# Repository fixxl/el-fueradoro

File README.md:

# el-fueradoro

This project contains a remotely controlled ignition system for audio-fireworks based on ATmega328P and RFM69CW.
Further information (in German) is given in [the user manual](https://cdn.jsdelivr.net/gh/fixxl/el-fueradoro@master/Manual/fueradoro.pdf).

What the system is capable of doing can be seen in our [new year's fireworks 2015](https://vimeo.com/116115628), [new year's fireworks 2016](https://vimeo.com/150594996), [new year's fireworks 2017](https://www.youtube.com/watch?v=Rc5oZRx3s50), [new year's fireworks 2018](https://www.youtube.com/watch?v=unH9tJSg1mw), and [new year's fireworks 2019](https://www.youtube.com/watch?v=GiKSdqZKpVQ).

Copyright:

All parts of the project are licensed under: https://creativecommons.org/licenses/by-nc/3.0/de/

Usage to perform commercial firework shows is explicitly granted.
Selling hard- and software derived from this project and usage within commercial systems is prohibited.

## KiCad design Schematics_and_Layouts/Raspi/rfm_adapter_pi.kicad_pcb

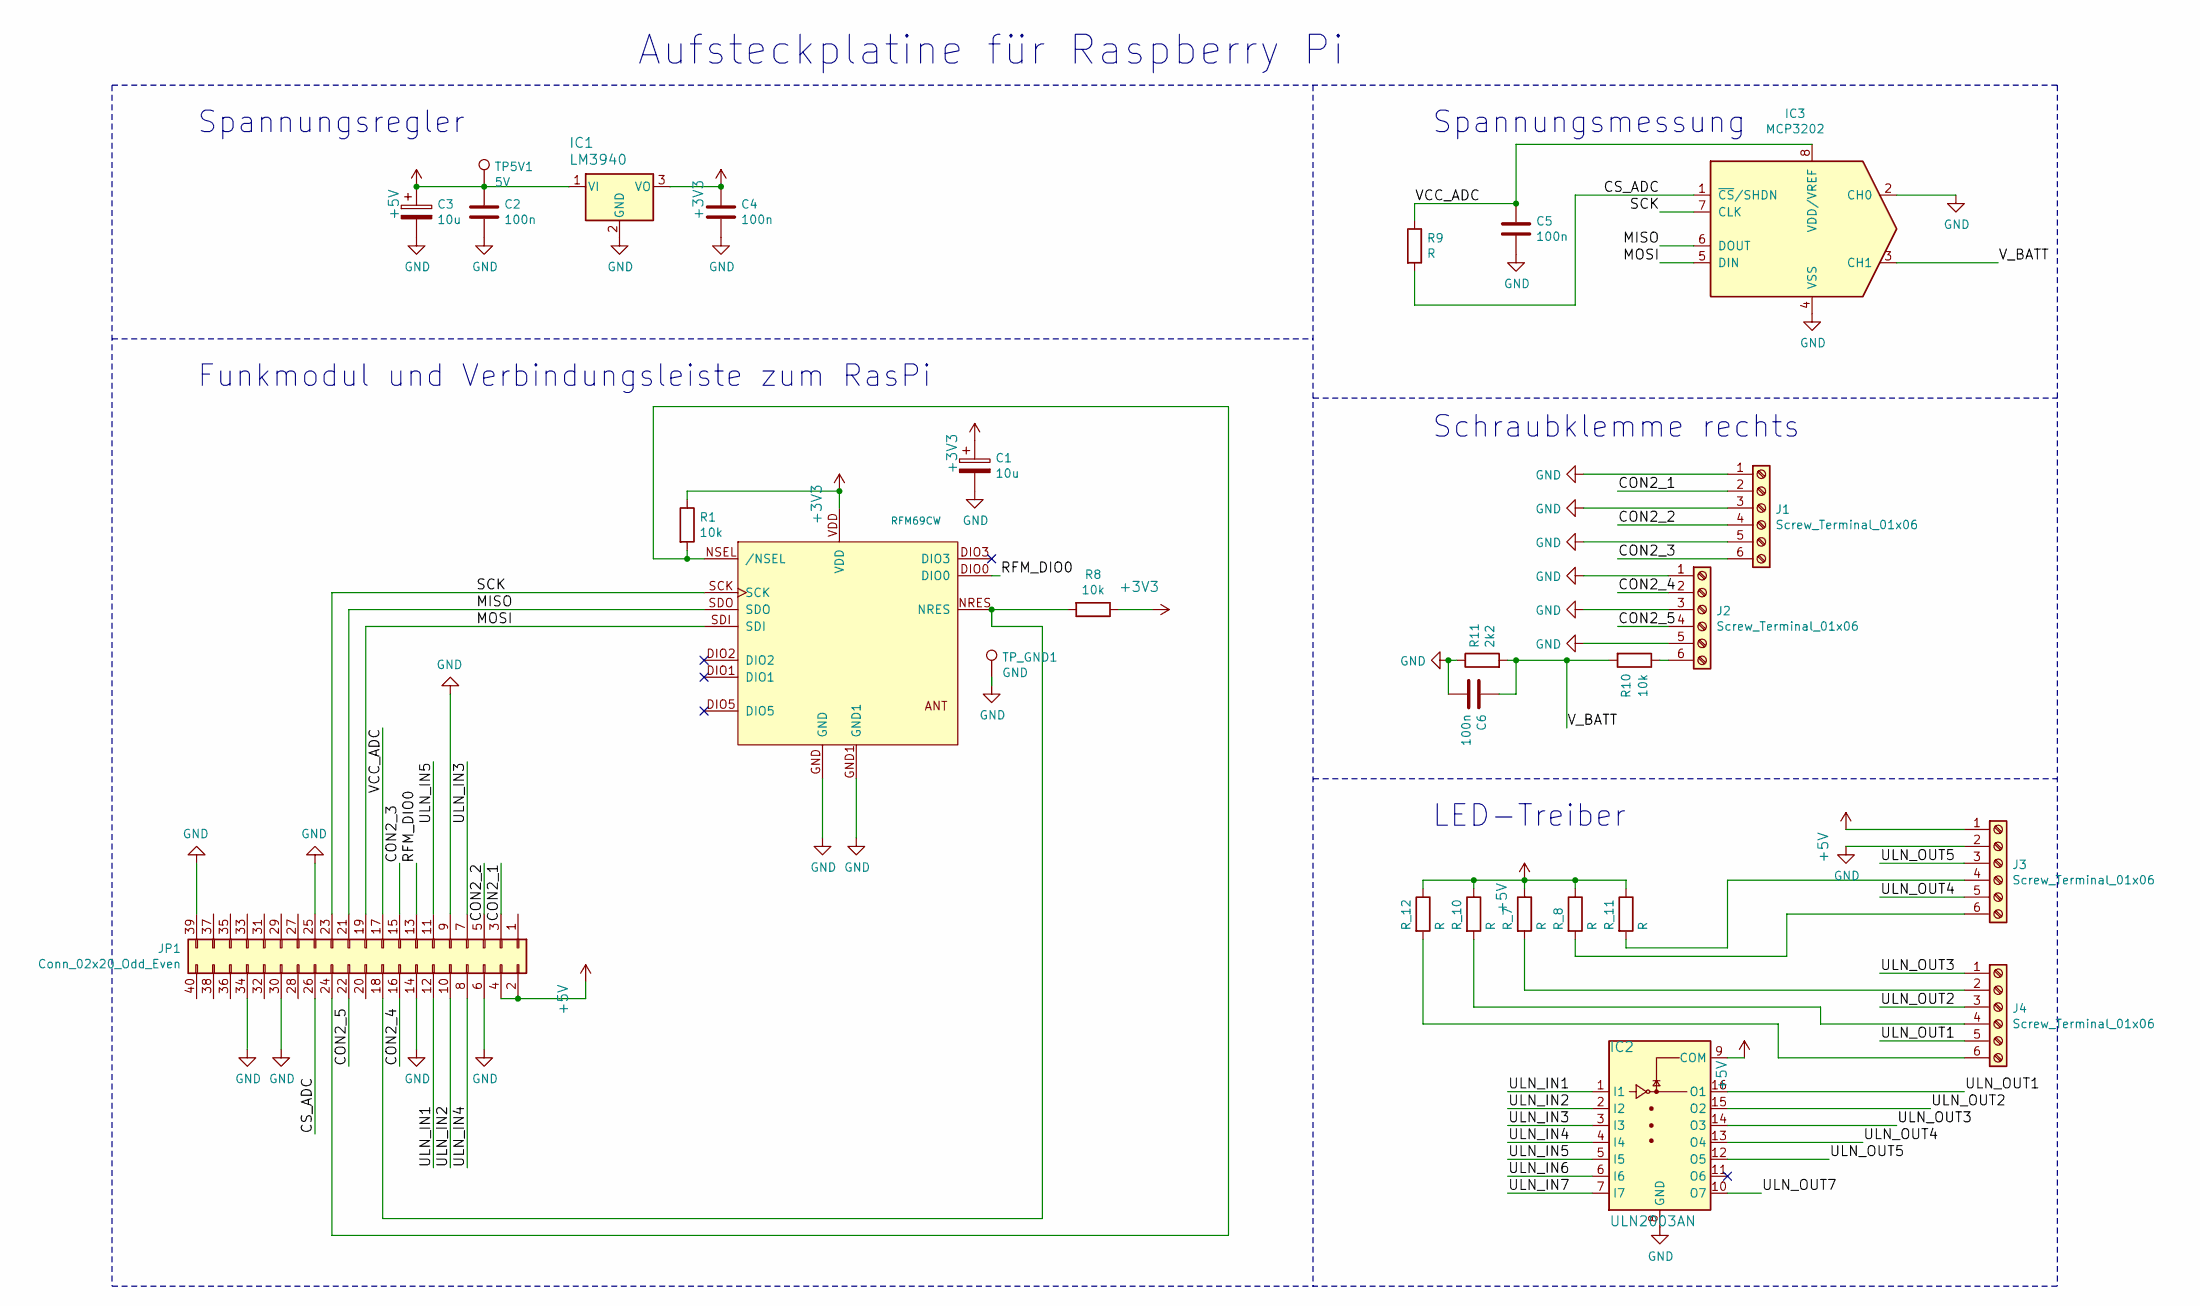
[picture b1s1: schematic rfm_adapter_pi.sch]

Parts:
C1, C3: 10u; CP_Radial_D5.0mm_P2.50mm
C2, C4, C5, C6: 100n; C_Disc_D5.0mm_W2.5mm_P2.50mm
IC1: LM3940; TO-220-3_Vertical
IC2: ULN2003AN; DIP-16_W7.62mm
IC3: MCP3202; DIP-8_W7.62mm
J1, J2, J3, J4: Screw_Terminal_01x06; TerminalBlock_MetzConnect_Type059_RT06306HBWC_1x06_P3.50mm
JP1: Conn_02x20_Odd_Even; PinSocket_2x20_P2.54mm_Vertical
R1, R8, R10: 10k; R_Axial_DIN0207_L6.3mm_D2.5mm_P10.16mm_Horizontal
R9: R; R_Axial_DIN0207_L6.3mm_D2.5mm_P10.16mm_Horizontal
R11: 2k2; R_Axial_DIN0207_L6.3mm_D2.5mm_P10.16mm_Horizontal
R_7, R_8, R_10, R_11, R_12: R; R_Axial_DIN0207_L6.3mm_D2.5mm_P10.16mm_Horizontal
TP5V1: 5V; TestPoint_THTPad_D1.5mm_Drill0.7mm
TP_GND1: GND; TestPoint_THTPad_D1.5mm_Drill0.7mm
U$1: RFM69CW

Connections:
+3V3: C1.1, C4.1, IC1.3 (VO), R1.1, R8.1, U$1.VDD
+5V: C2.1, C3.1, IC1.1 (VI), IC2.9 (COM), J3.1, JP1.2, JP1.4, R_7.1, R_8.1, R_10.1, R_11.1, R_12.1, TP5V1.1
/CON2_1: J1.2, JP1.3
/CON2_2: J1.4, JP1.5
/CON2_3: J1.6, JP1.15
/CON2_4: J2.2, JP1.16
/CON2_5: J2.4, JP1.22
/CS_ADC: IC3.1 (~CS~/SHDN), JP1.26, R9.2
/MISO: IC3.6 (DOUT), JP1.21, U$1.SDO
/MOSI: IC3.5 (DIN), JP1.19, U$1.SDI
/RFM_DIO0: JP1.13, U$1.DIO0
/SCK: IC3.7 (CLK), JP1.23, U$1.SCK
/ULN_IN1: IC2.1 (I1), JP1.12
/ULN_IN2: IC2.2 (I2), JP1.10
/ULN_IN3: IC2.3 (I3), JP1.7
/ULN_IN4: IC2.4 (I4), JP1.8
/ULN_IN5: IC2.5 (I5), JP1.11
/ULN_IN6: IC2.6 (I6)
/ULN_IN7: IC2.7 (I7)
/ULN_OUT1: IC2.16 (O1), J4.5
/ULN_OUT2: IC2.15 (O2), J4.3
/ULN_OUT3: IC2.14 (O3), J4.1
/ULN_OUT4: IC2.13 (O4), J3.5
/ULN_OUT5: IC2.12 (O5), J3.3
/ULN_OUT7: IC2.10 (O7)
/VCC_ADC: C5.1, IC3.8 (VDD/VREF), JP1.17, R9.1
/V_BATT: C6.1, IC3.3 (CH1), R10.2, R11.2
GND: C1.2, C2.2, C3.2, C4.2, C5.2, C6.2, IC1.2 (GND), IC2.8 (GND), IC3.2 (CH0), IC3.4 (VSS), J1.1, J1.3, J1.5, J2.1, J2.3, J2.5, J3.2, JP1.6, JP1.9, JP1.14, JP1.25, JP1.30, JP1.34, JP1.39, R11.1, TP_GND1.1, U$1.GND, U$1.GND1
unnamed: J2.6, R10.1
unnamed: J3.4, R_11.2
unnamed: J3.6, R_8.2
unnamed: J4.2, R_7.2
unnamed: J4.4, R_10.2
unnamed: J4.6, R_12.2
unnamed: JP1.18, R8.2, U$1.NRES
unnamed: JP1.24, R1.2, U$1.NSEL (/NSEL)

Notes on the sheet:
Aufsteckplatine für Raspberry Pi
LED-Treiber
Schraubklemme rechts
Spannungsmessung
Spannungsregler
Funkmodul und Verbindungsleiste zum RasPi

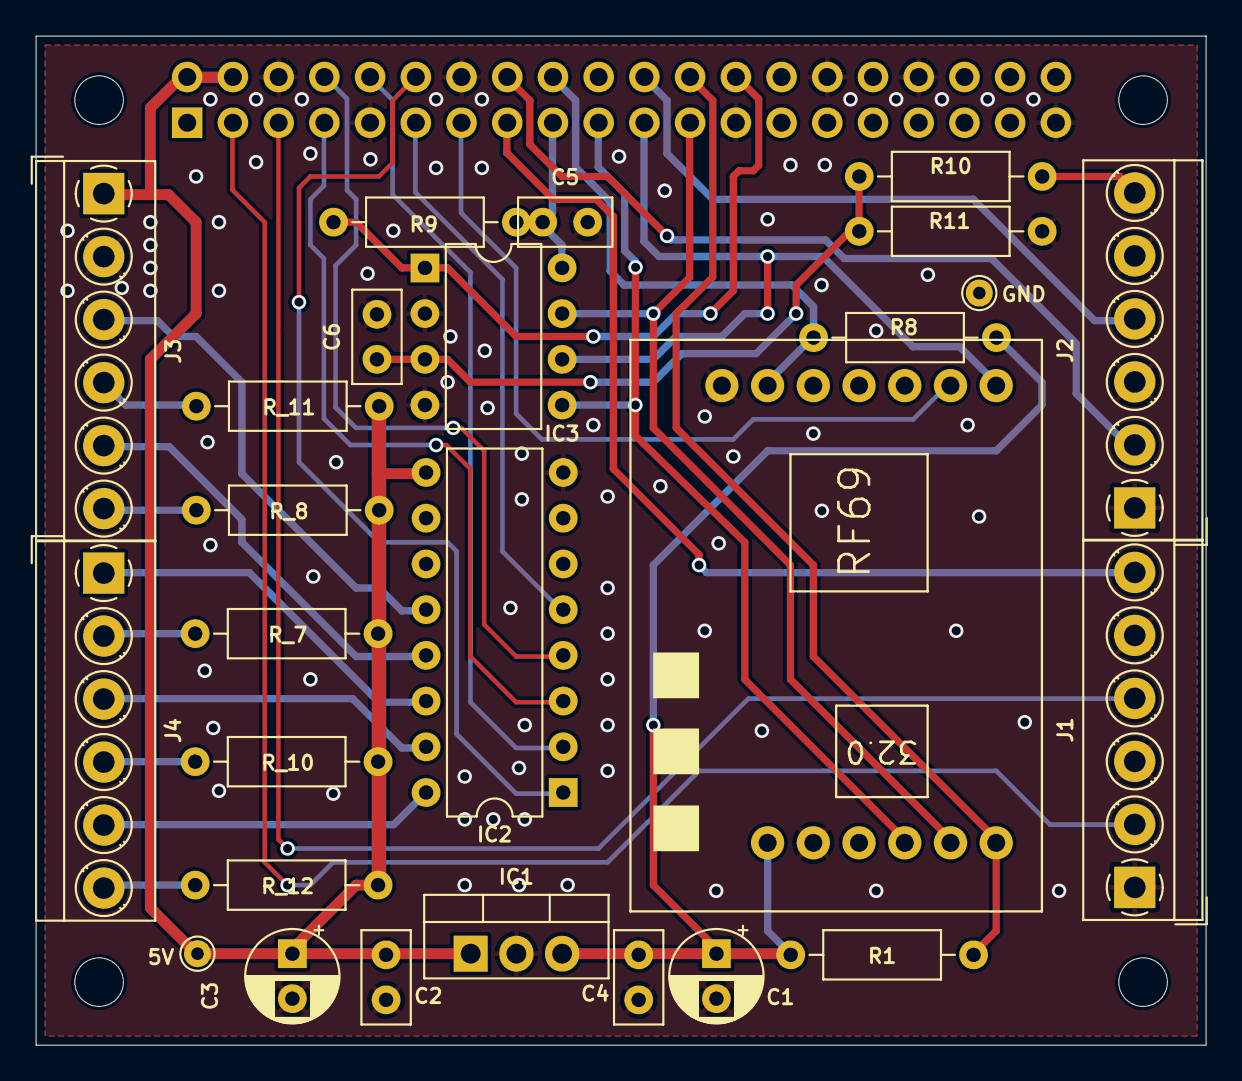
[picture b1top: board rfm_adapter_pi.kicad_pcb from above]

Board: 2 copper layers, 65.0 x 56.1 mm, 27 parts (0 on the bottom side), 33 nets.

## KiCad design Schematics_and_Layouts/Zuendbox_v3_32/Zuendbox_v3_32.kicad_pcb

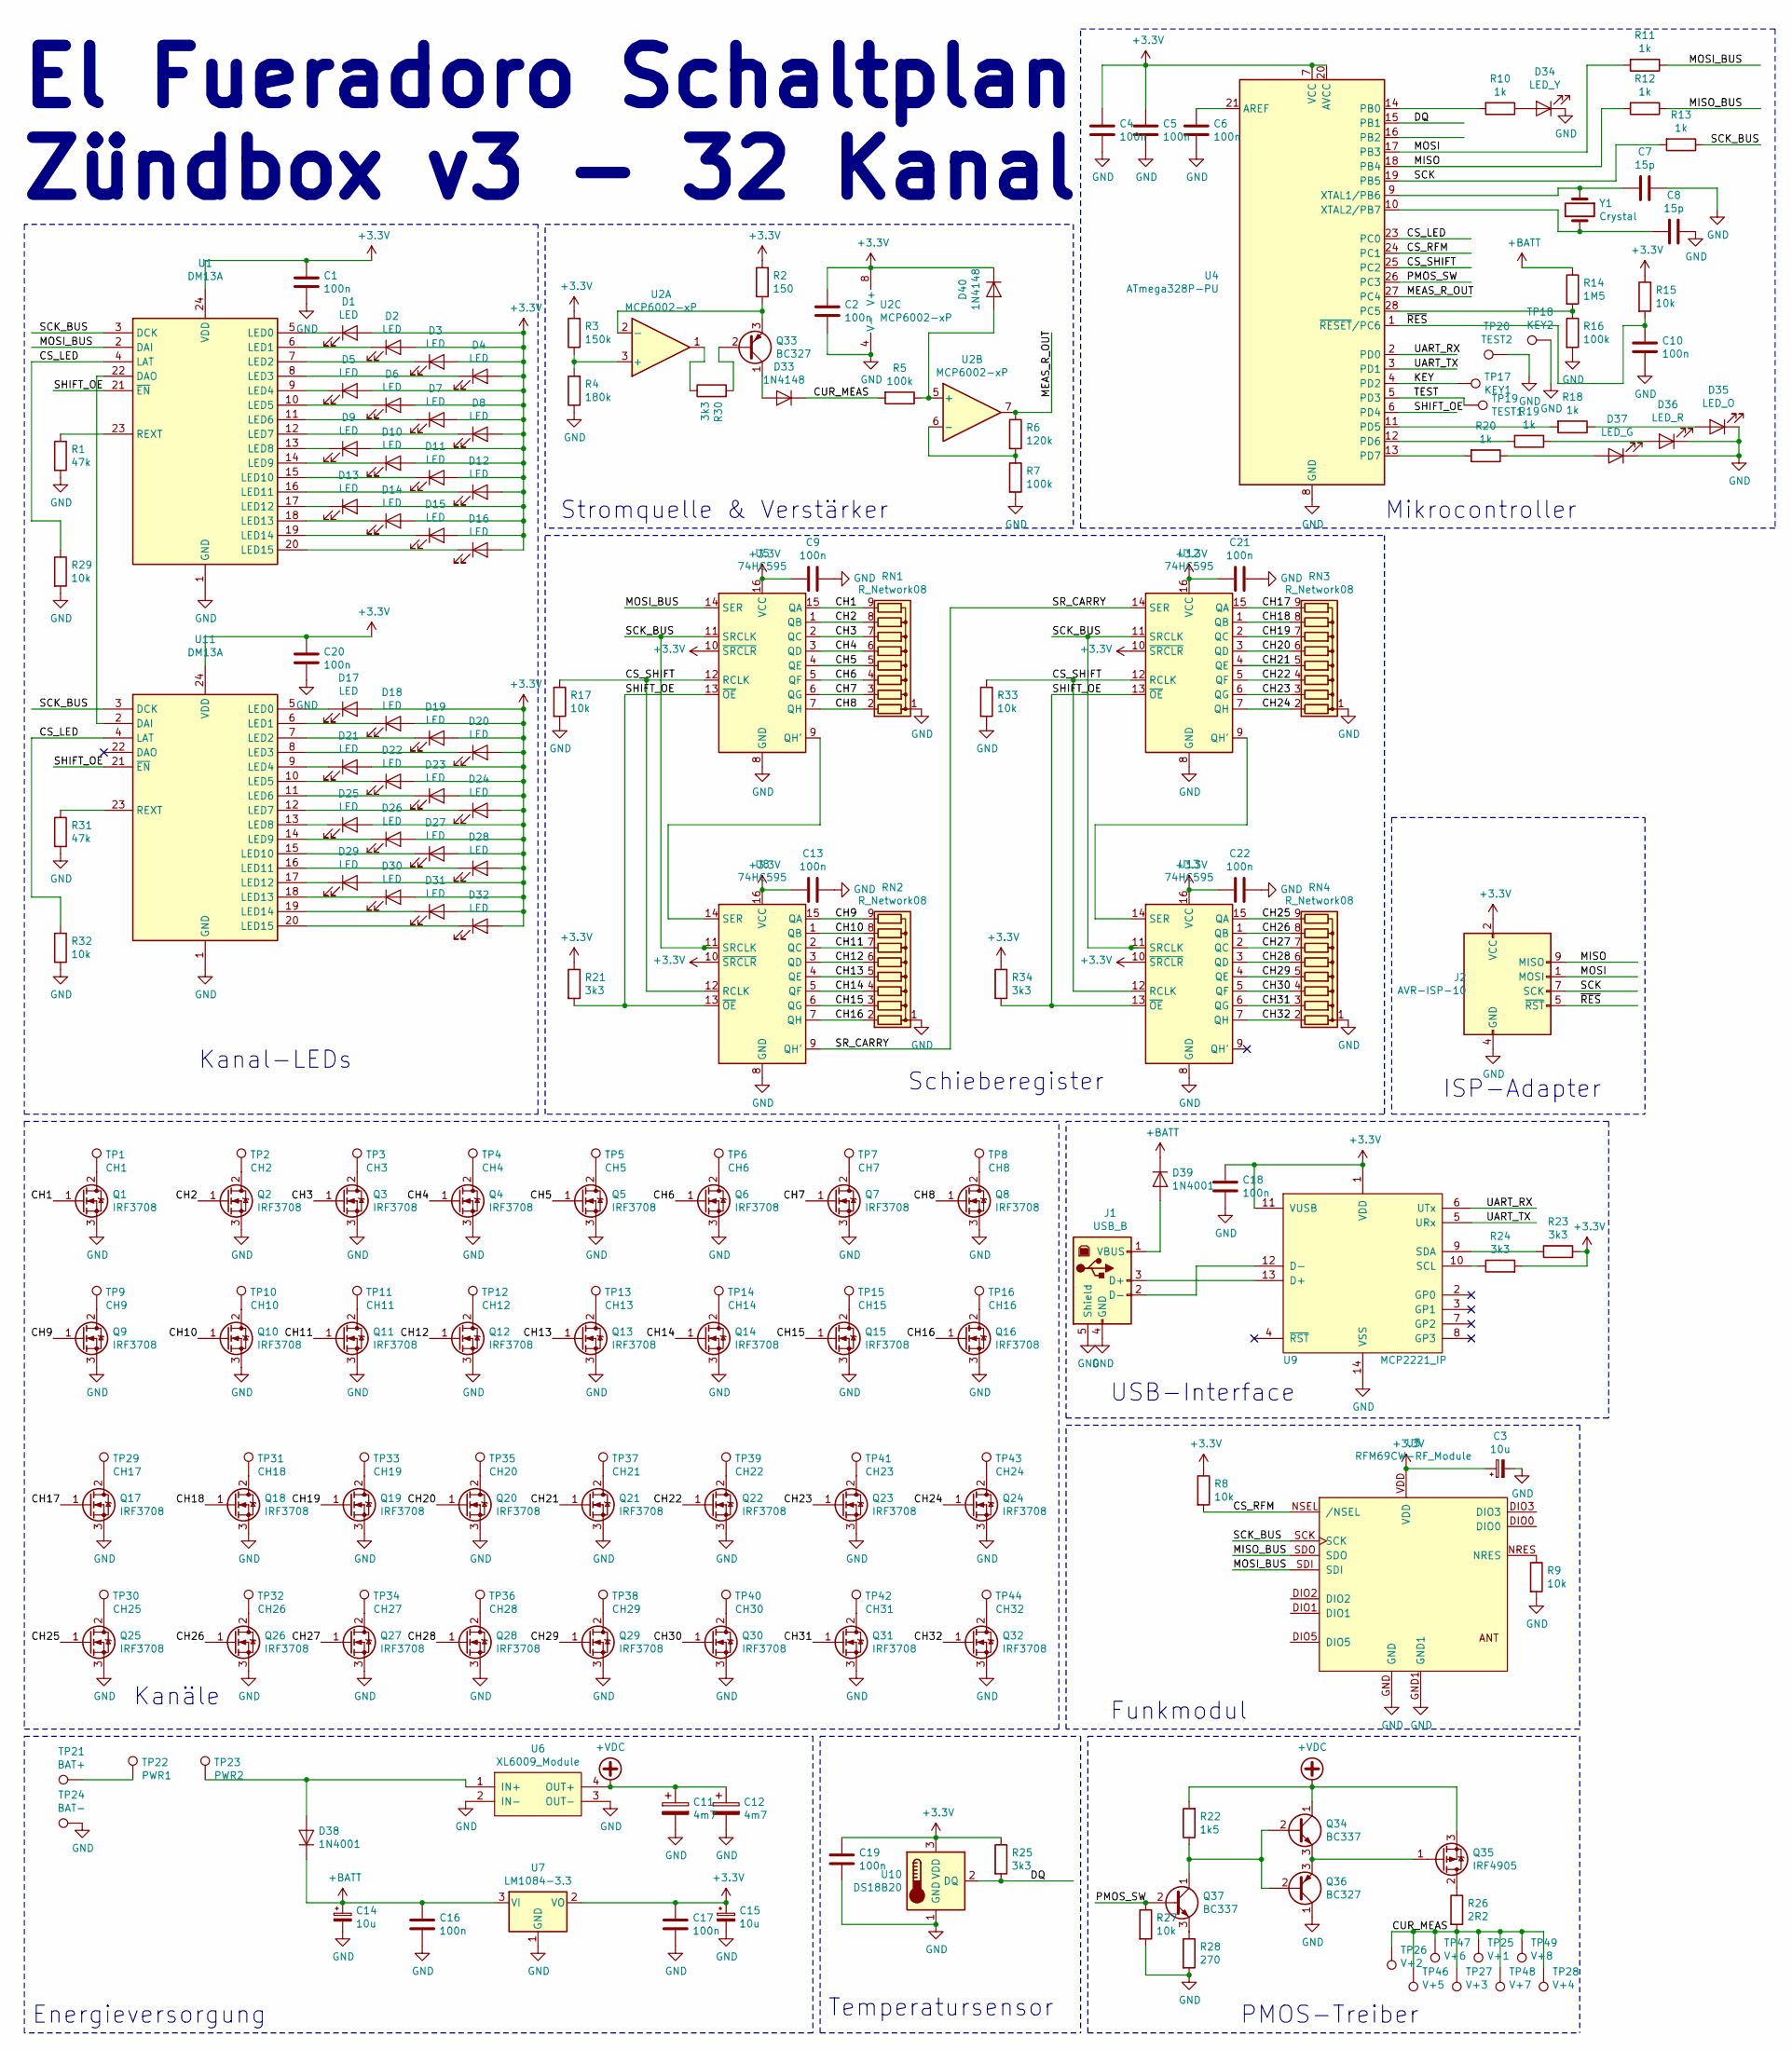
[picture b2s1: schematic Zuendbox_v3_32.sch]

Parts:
C1, C2, C4, C5, C6, C9, C10, C13, C16, C17, C18, C19, C20, C21, C22: 100n; C_Disc_D3.8mm_W2.6mm_P2.50mm
C3, C14, C15: 10u; CP_Radial_D6.3mm_P2.50mm
C7, C8: 15p; C_Disc_D3.8mm_W2.6mm_P2.50mm
C11, C12: 4m7; CP_Radial_D18.0mm_P7.50mm
D1, D2, D3, D4, D5, D6, D7, D8, D9, D10, D11, D12, D13, D14, D15, D16, D17, D18, D19, D20, D21, D22, D23, D24, D25, D26, D27, D28, D29, D30, D31, D32: LED; PinSocket_1x02_P2.54mm_Vertical
D33, D40: 1N4148; D_DO-35_SOD27_P7.62mm_Horizontal
D34: LED_Y; LED_D5.0mm
D35: LED_O; LED_D5.0mm
D36: LED_R; LED_D5.0mm
D37: LED_G; LED_D5.0mm
D38, D39: 1N4001; D_DO-41_SOD81_P10.16mm_Horizontal
J1: USB_B; USB_B_THT_Horizontal
J2: AVR-ISP-10; IDC-Header_2x05_P2.54mm_Vertical
Q1, Q2, Q3, Q4, Q5, Q6, Q7, Q8, Q9, Q10, Q11, Q12, Q13, Q14, Q15, Q16, Q17, Q18, Q19, Q20, Q21, Q22, Q23, Q24, Q25, Q26, Q27, Q28, Q29, Q30, Q31, Q32: IRF3708; TO-220-3_Vertical
Q33, Q36: BC327; TO-92_Inline_Wide
Q34, Q37: BC337; TO-92_Inline_Wide
Q35: IRF4905; TO-220-3_Vertical
R1, R31: 47k; R_Axial_DIN0207_L6.3mm_D2.5mm_P10.16mm_Horizontal
R2: 150; R_Axial_DIN0207_L6.3mm_D2.5mm_P10.16mm_Horizontal
R3: 150k; R_Axial_DIN0207_L6.3mm_D2.5mm_P10.16mm_Horizontal
R4: 180k; R_Axial_DIN0207_L6.3mm_D2.5mm_P10.16mm_Horizontal
R5, R7, R16: 100k; R_Axial_DIN0207_L6.3mm_D2.5mm_P10.16mm_Horizontal
R6: 120k; R_Axial_DIN0207_L6.3mm_D2.5mm_P10.16mm_Horizontal
R8, R9, R15, R17, R27, R29, R32, R33: 10k; R_Axial_DIN0207_L6.3mm_D2.5mm_P10.16mm_Horizontal
R10, R11, R12, R13, R18, R19, R20: 1k; R_Axial_DIN0207_L6.3mm_D2.5mm_P10.16mm_Horizontal
R14: 1M5; R_Axial_DIN0207_L6.3mm_D2.5mm_P10.16mm_Horizontal
R21, R23, R24, R25, R30, R34: 3k3; R_Axial_DIN0207_L6.3mm_D2.5mm_P10.16mm_Horizontal
R22: 1k5; R_Axial_DIN0207_L6.3mm_D2.5mm_P10.16mm_Horizontal
R26: 2R2; R_Radial_Power_L9.0mm_W10.0mm_Px2.90mm_Py2.40mm
R28: 270; R_Axial_DIN0207_L6.3mm_D2.5mm_P10.16mm_Horizontal
RN1, RN2, RN3, RN4: R_Network08; R_Array_SIP9
TP1: CH1; TestPoint_THTPad_D2.5mm_Drill1.2mm
TP2: CH2; TestPoint_THTPad_D2.5mm_Drill1.2mm
TP3: CH3; TestPoint_THTPad_D2.5mm_Drill1.2mm
TP4: CH4; TestPoint_THTPad_D2.5mm_Drill1.2mm
TP5: CH5; TestPoint_THTPad_D2.5mm_Drill1.2mm
TP6: CH6; TestPoint_THTPad_D2.5mm_Drill1.2mm
TP7: CH7; TestPoint_THTPad_D2.5mm_Drill1.2mm
TP8: CH8; TestPoint_THTPad_D2.5mm_Drill1.2mm
TP9: CH9; TestPoint_THTPad_D2.5mm_Drill1.2mm
TP10: CH10; TestPoint_THTPad_D2.5mm_Drill1.2mm
TP11: CH11; TestPoint_THTPad_D2.5mm_Drill1.2mm
TP12: CH12; TestPoint_THTPad_D2.5mm_Drill1.2mm
TP13: CH13; TestPoint_THTPad_D2.5mm_Drill1.2mm
TP14: CH14; TestPoint_THTPad_D2.5mm_Drill1.2mm
TP15: CH15; TestPoint_THTPad_D2.5mm_Drill1.2mm
TP16: CH16; TestPoint_THTPad_D2.5mm_Drill1.2mm
TP17: KEY1; TestPoint_THTPad_D2.5mm_Drill1.2mm
TP18: KEY2; TestPoint_THTPad_D2.5mm_Drill1.2mm
TP19: TEST1; TestPoint_THTPad_D2.5mm_Drill1.2mm
TP20: TEST2; TestPoint_THTPad_D2.5mm_Drill1.2mm
TP21: BAT+; TestPoint_THTPad_D2.5mm_Drill1.2mm
TP22: PWR1; TestPoint_THTPad_D2.5mm_Drill1.2mm
TP23: PWR2; TestPoint_THTPad_D2.5mm_Drill1.2mm
TP24: BAT-; TestPoint_THTPad_D2.5mm_Drill1.2mm
TP25: V+1; TestPoint_THTPad_D2.5mm_Drill1.2mm
TP26: V+2; TestPoint_THTPad_D2.5mm_Drill1.2mm
TP27: V+3; TestPoint_THTPad_D2.5mm_Drill1.2mm
TP28: V+4; TestPoint_THTPad_D2.5mm_Drill1.2mm
TP29: CH17; TestPoint_THTPad_D2.5mm_Drill1.2mm
TP30: CH25; TestPoint_THTPad_D2.5mm_Drill1.2mm
TP31: CH18; TestPoint_THTPad_D2.5mm_Drill1.2mm
TP32: CH26; TestPoint_THTPad_D2.5mm_Drill1.2mm
TP33: CH19; TestPoint_THTPad_D2.5mm_Drill1.2mm
TP34: CH27; TestPoint_THTPad_D2.5mm_Drill1.2mm
TP35: CH20; TestPoint_THTPad_D2.5mm_Drill1.2mm
TP36: CH28; TestPoint_THTPad_D2.5mm_Drill1.2mm
TP37: CH21; TestPoint_THTPad_D2.5mm_Drill1.2mm
TP38: CH29; TestPoint_THTPad_D2.5mm_Drill1.2mm
TP39: CH22; TestPoint_THTPad_D2.5mm_Drill1.2mm
TP40: CH30; TestPoint_THTPad_D2.5mm_Drill1.2mm
TP41: CH23; TestPoint_THTPad_D2.5mm_Drill1.2mm
TP42: CH31; TestPoint_THTPad_D2.5mm_Drill1.2mm
TP43: CH24; TestPoint_THTPad_D2.5mm_Drill1.2mm
TP44: CH32; TestPoint_THTPad_D2.5mm_Drill1.2mm
TP46: V+5; TestPoint_THTPad_D2.5mm_Drill1.2mm
TP47: V+6; TestPoint_THTPad_D2.5mm_Drill1.2mm
TP48: V+7; TestPoint_THTPad_D2.5mm_Drill1.2mm
TP49: V+8; TestPoint_THTPad_D2.5mm_Drill1.2mm
U1, U11: DM13A; DIP-24_W7.62mm
U2: MCP6002-xP; DIP-8_W7.62mm
U3: RFM69CW-RF_Module; RFM69CW
U4: ATmega328P-PU; DIP-28_W7.62mm
U5, U8, U12, U13: 74HC595; DIP-16_W7.62mm
U6: XL6009_Module; XL6009_STEP-UP-MODULE
U7: LM1084-3.3; TO-220-3_Horizontal_TabDown
U9: MCP2221_IP; DIP-14_W7.62mm
U10: DS18B20; TO-92_Inline_Wide
Y1: Crystal; Crystal_HC49-U_Vertical

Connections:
+3V3: C1.1, C2.1, C3.1, C4.2, C5.2, C9.2, C13.2, C15.1, C17.2, C18.2, C19.2, C20.1, C21.2, C22.2, D1.2 (A), D2.2 (A), D3.2 (A), D4.2 (A), D5.2 (A), D6.2 (A), D7.2 (A), D8.2 (A), D9.2 (A), D10.2 (A), D11.2 (A), D12.2 (A), D13.2 (A), D14.2 (A), D15.2 (A), D16.2 (A), D17.2 (A), D18.2 (A), D19.2 (A), D20.2 (A), D21.2 (A), D22.2 (A), D23.2 (A), D24.2 (A), D25.2 (A), D26.2 (A), D27.2 (A), D28.2 (A), D29.2 (A), D30.2 (A), D31.2 (A), D32.2 (A), D40.1 (K), J2.2 (VCC), R2.2, R3.2, R8.1, R15.1, R21.1, R23.2, R24.2, R25.1, R34.1, U1.24 (VDD), U2.8 (V+), U3.VDD, U4.7 (VCC), U4.20 (AVCC), U5.10 (~SRCLR), U5.16 (VCC), U7.2 (VO), U8.10 (~SRCLR), U8.16 (VCC), U9.1 (VDD), U9.11 (VUSB), U10.3 (VDD), U11.24 (VDD), U12.10 (~SRCLR), U12.16 (VCC), U13.10 (~SRCLR), U13.16 (VCC)
+BATT: C14.1, C16.2, D38.1 (K), D39.1 (K), R14.1, U7.3 (VI)
+VDC: C11.1, C12.1, Q34.1 (C), Q35.3 (S), R22.2, U6.4 (OUT+)
/CH1: Q1.1 (G), RN1.9 (R8), U5.15 (QA)
/CH2: Q2.1 (G), RN1.8 (R7), U5.1 (QB)
/CH3: Q3.1 (G), RN1.7 (R6), U5.2 (QC)
/CH4: Q4.1 (G), RN1.6 (R5), U5.3 (QD)
/CH5: Q5.1 (G), RN1.5 (R4), U5.4 (QE)
/CH6: Q6.1 (G), RN1.4 (R3), U5.5 (QF)
/CH7: Q7.1 (G), RN1.3 (R2), U5.6 (QG)
/CH8: Q8.1 (G), RN1.2 (R1), U5.7 (QH)
/CH9: Q9.1 (G), RN2.9 (R8), U8.15 (QA)
/CH10: Q10.1 (G), RN2.8 (R7), U8.1 (QB)
/CH11: Q11.1 (G), RN2.7 (R6), U8.2 (QC)
/CH12: Q12.1 (G), RN2.6 (R5), U8.3 (QD)
/CH13: Q13.1 (G), RN2.5 (R4), U8.4 (QE)
/CH14: Q14.1 (G), RN2.4 (R3), U8.5 (QF)
/CH15: Q15.1 (G), RN2.3 (R2), U8.6 (QG)
/CH16: Q16.1 (G), RN2.2 (R1), U8.7 (QH)
/CH17: Q17.1 (G), RN3.9 (R8), U12.15 (QA)
/CH18: Q18.1 (G), RN3.8 (R7), U12.1 (QB)
/CH19: Q19.1 (G), RN3.7 (R6), U12.2 (QC)
/CH20: Q20.1 (G), RN3.6 (R5), U12.3 (QD)
/CH21: Q21.1 (G), RN3.5 (R4), U12.4 (QE)
/CH22: Q22.1 (G), RN3.4 (R3), U12.5 (QF)
/CH23: Q23.1 (G), RN3.3 (R2), U12.6 (QG)
/CH24: Q24.1 (G), RN3.2 (R1), U12.7 (QH)
/CH25: Q25.1 (G), RN4.9 (R8), U13.15 (QA)
/CH26: Q26.1 (G), RN4.8 (R7), U13.1 (QB)
/CH27: Q27.1 (G), RN4.7 (R6), U13.2 (QC)
/CH28: Q28.1 (G), RN4.6 (R5), U13.3 (QD)
/CH29: Q29.1 (G), RN4.5 (R4), U13.4 (QE)
/CH30: Q30.1 (G), RN4.4 (R3), U13.5 (QF)
/CH31: Q31.1 (G), RN4.3 (R2), U13.6 (QG)
/CH32: Q32.1 (G), RN4.2 (R1), U13.7 (QH)
/CS_LED: R29.1, R32.1, U1.4 (LAT), U4.23 (PC0), U11.4 (LAT)
/CS_RFM: R8.2, U3.NSEL (/NSEL), U4.24 (PC1)
/CS_SHIFT: R17.1, R33.1, U4.25 (PC2), U5.12 (RCLK), U8.12 (RCLK), U12.12 (RCLK), U13.12 (RCLK)
/CUR_MEAS: D33.1 (K), R5.2, R26.2, TP25.1, TP26.1, TP27.1, TP28.1, TP46.1, TP47.1, TP48.1, TP49.1
/DQ: R25.2, U4.15 (PB1), U10.2 (DQ)
/KEY: TP17.1, U4.4 (PD2)
/MEAS_R_OUT: R6.1, U2.7, U4.27 (PC4)
/MISO: J2.9 (MISO), R12.2, U4.18 (PB4)
/MISO_BUS: R12.1, U3.SDO
/MOSI: J2.1 (MOSI), R11.2, U4.17 (PB3)
/MOSI_BUS: R11.1, U1.2 (DAI), U3.SDI, U5.14 (SER)
/PMOS_SW: Q37.2 (B), R27.1, U4.26 (PC3)
/SCK: J2.7 (SCK), R13.2, U4.19 (PB5)
/SCK_BUS: R13.1, U1.3 (DCK), U3.SCK, U5.11 (SRCLK), U8.11 (SRCLK), U11.3 (DCK), U12.11 (SRCLK), U13.11 (SRCLK)
/SHIFT_OE: R21.2, R34.2, U1.21 (~EN), U4.6 (PD4), U5.13 (~OE), U8.13 (~OE), U11.21 (~EN), U12.13 (~OE), U13.13 (~OE)
/SR_CARRY: U8.9 (QH'), U12.14 (SER)
/TEST: TP19.1, U4.5 (PD3)
/UART_RX: U4.2 (PD0), U9.6 (UTx)
/UART_TX: U4.3 (PD1), U9.5 (URx)
/~RES: C10.2, J2.5 (~RST), R15.2, U4.1 (~RESET~/PC6)
GND: C1.2, C2.2, C3.2, C4.1, C5.1, C6.1, C7.1, C8.1, C9.1, C10.1, C11.2, C12.2, C13.1, C14.2, C15.2, C16.1, C17.1, C18.1, C19.1, C20.2, C21.1, C22.1, D34.1 (K), D35.1 (K), D36.1 (K), D37.1 (K), J1.4 (GND), J1.5 (Shield), J2.4 (GND), J2.6 (GND), J2.8 (GND), J2.10 (GND), Q1.3 (S), Q2.3 (S), Q3.3 (S), Q4.3 (S), Q5.3 (S), Q6.3 (S), Q7.3 (S), Q8.3 (S), Q9.3 (S), Q10.3 (S), Q11.3 (S), Q12.3 (S), Q13.3 (S), Q14.3 (S), Q15.3 (S), Q16.3 (S), Q17.3 (S), Q18.3 (S), Q19.3 (S), Q20.3 (S), Q21.3 (S), Q22.3 (S), Q23.3 (S), Q24.3 (S), Q25.3 (S), Q26.3 (S), Q27.3 (S), Q28.3 (S), Q29.3 (S), Q30.3 (S), Q31.3 (S), Q32.3 (S), Q36.1 (C), R1.2, R4.1, R7.2, R9.2, R16.2, R17.2, R27.2, R28.2, R29.2, R31.2, R32.2, R33.2, RN1.1 (common), RN2.1 (common), RN3.1 (common), RN4.1 (common), TP18.1, TP20.1, TP24.1, U1.1 (GND), U2.4 (V-), U3.GND, U3.GND1, U4.8 (GND), U4.22 (GND), U5.8 (GND), U6.2 (IN-), U6.3 (OUT-), U7.1 (GND), U8.8 (GND), U9.14 (VSS), U10.1 (GND), U11.1 (GND), U12.8 (GND), U13.8 (GND)
unnamed: C6.2, U4.21 (AREF)
unnamed: C7.2, U4.9 (XTAL1/PB6), Y1.1
unnamed: C8.2, U4.10 (XTAL2/PB7), Y1.2
unnamed: D1.1 (K), U1.5 (LED0)
unnamed: D2.1 (K), U1.6 (LED1)
unnamed: D3.1 (K), U1.7 (LED2)
unnamed: D4.1 (K), U1.8 (LED3)
unnamed: D5.1 (K), U1.9 (LED4)
unnamed: D6.1 (K), U1.10 (LED5)
unnamed: D7.1 (K), U1.11 (LED6)
unnamed: D8.1 (K), U1.12 (LED7)
unnamed: D9.1 (K), U1.13 (LED8)
unnamed: D10.1 (K), U1.14 (LED9)
unnamed: D11.1 (K), U1.15 (LED10)
unnamed: D12.1 (K), U1.16 (LED11)
unnamed: D13.1 (K), U1.17 (LED12)
unnamed: D14.1 (K), U1.18 (LED13)
unnamed: D15.1 (K), U1.19 (LED14)
unnamed: D16.1 (K), U1.20 (LED15)
unnamed: D17.1 (K), U11.5 (LED0)
unnamed: D18.1 (K), U11.6 (LED1)
unnamed: D19.1 (K), U11.7 (LED2)
unnamed: D20.1 (K), U11.8 (LED3)
unnamed: D21.1 (K), U11.9 (LED4)
unnamed: D22.1 (K), U11.10 (LED5)
unnamed: D23.1 (K), U11.11 (LED6)
unnamed: D24.1 (K), U11.12 (LED7)
unnamed: D25.1 (K), U11.13 (LED8)
unnamed: D26.1 (K), U11.14 (LED9)
unnamed: D27.1 (K), U11.15 (LED10)
unnamed: D28.1 (K), U11.16 (LED11)
unnamed: D29.1 (K), U11.17 (LED12)
unnamed: D30.1 (K), U11.18 (LED13)
unnamed: D31.1 (K), U11.19 (LED14)
unnamed: D32.1 (K), U11.20 (LED15)
unnamed: D33.2 (A), Q33.1 (C)
unnamed: D34.2 (A), R10.1
unnamed: D35.2 (A), R18.1
unnamed: D36.2 (A), R19.1
unnamed: D37.2 (A), R20.1
unnamed: D38.2 (A), TP23.1, U6.1 (IN+)
unnamed: D39.2 (A), J1.1 (VBUS)
unnamed: D40.2 (A), R5.1, U2.5 (+)
unnamed: J1.2 (D-), U9.12 (D-)
unnamed: J1.3 (D+), U9.13 (D+)
unnamed: Q1.2 (D), TP1.1
unnamed: Q2.2 (D), TP2.1
unnamed: Q3.2 (D), TP3.1
unnamed: Q4.2 (D), TP4.1
unnamed: Q5.2 (D), TP5.1
unnamed: Q6.2 (D), TP6.1
unnamed: Q7.2 (D), TP7.1
unnamed: Q8.2 (D), TP8.1
unnamed: Q9.2 (D), TP9.1
unnamed: Q10.2 (D), TP10.1
unnamed: Q11.2 (D), TP11.1
unnamed: Q12.2 (D), TP12.1
unnamed: Q13.2 (D), TP13.1
unnamed: Q14.2 (D), TP14.1
unnamed: Q15.2 (D), TP15.1
unnamed: Q16.2 (D), TP16.1
unnamed: Q17.2 (D), TP29.1
unnamed: Q18.2 (D), TP31.1
unnamed: Q19.2 (D), TP33.1
unnamed: Q20.2 (D), TP35.1
unnamed: Q21.2 (D), TP37.1
unnamed: Q22.2 (D), TP39.1
unnamed: Q23.2 (D), TP41.1
unnamed: Q24.2 (D), TP43.1
unnamed: Q25.2 (D), TP30.1
unnamed: Q26.2 (D), TP32.1
unnamed: Q27.2 (D), TP34.1
unnamed: Q28.2 (D), TP36.1
unnamed: Q29.2 (D), TP38.1
unnamed: Q30.2 (D), TP40.1
unnamed: Q31.2 (D), TP42.1
unnamed: Q32.2 (D), TP44.1
unnamed: Q33.2 (B), R30.2
unnamed: Q33.3 (E), R2.1, U2.2 (-)
unnamed: Q34.2 (B), Q36.2 (B), Q37.1 (C), R22.1
unnamed: Q34.3 (E), Q35.1 (G), Q36.3 (E)
unnamed: Q35.2 (D), R26.1
unnamed: Q37.3 (E), R28.1
unnamed: R1.1, U1.23 (REXT)
unnamed: R3.1, R4.2, U2.3 (+)
unnamed: R6.2, R7.1, U2.6 (-)
unnamed: R9.1, U3.NRES
unnamed: R10.2, U4.14 (PB0)
unnamed: R14.2, R16.1, U4.28 (PC5)
unnamed: R18.2, U4.11 (PD5)
unnamed: R19.2, U4.12 (PD6)
unnamed: R20.2, U4.13 (PD7)
unnamed: R23.1, U9.9 (SDA)
unnamed: R24.1, U9.10 (SCL)
unnamed: R30.1, U2.1
unnamed: R31.1, U11.23 (REXT)
unnamed: TP21.1, TP22.1
unnamed: U1.22 (DAO), U11.2 (DAI)
unnamed: U5.9 (QH'), U8.14 (SER)
unnamed: U12.9 (QH'), U13.14 (SER)

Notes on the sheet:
El Fueradoro Schaltplan Zündbox v3 - 32 Kanal
Temperatursensor
PMOS-Treiber
Funkmodul
Schieberegister
Stromquelle & Verstärker
Energieversorgung
Mikrocontroller
ISP-Adapter
USB-Interface
Kanäle
Kanal-LEDs

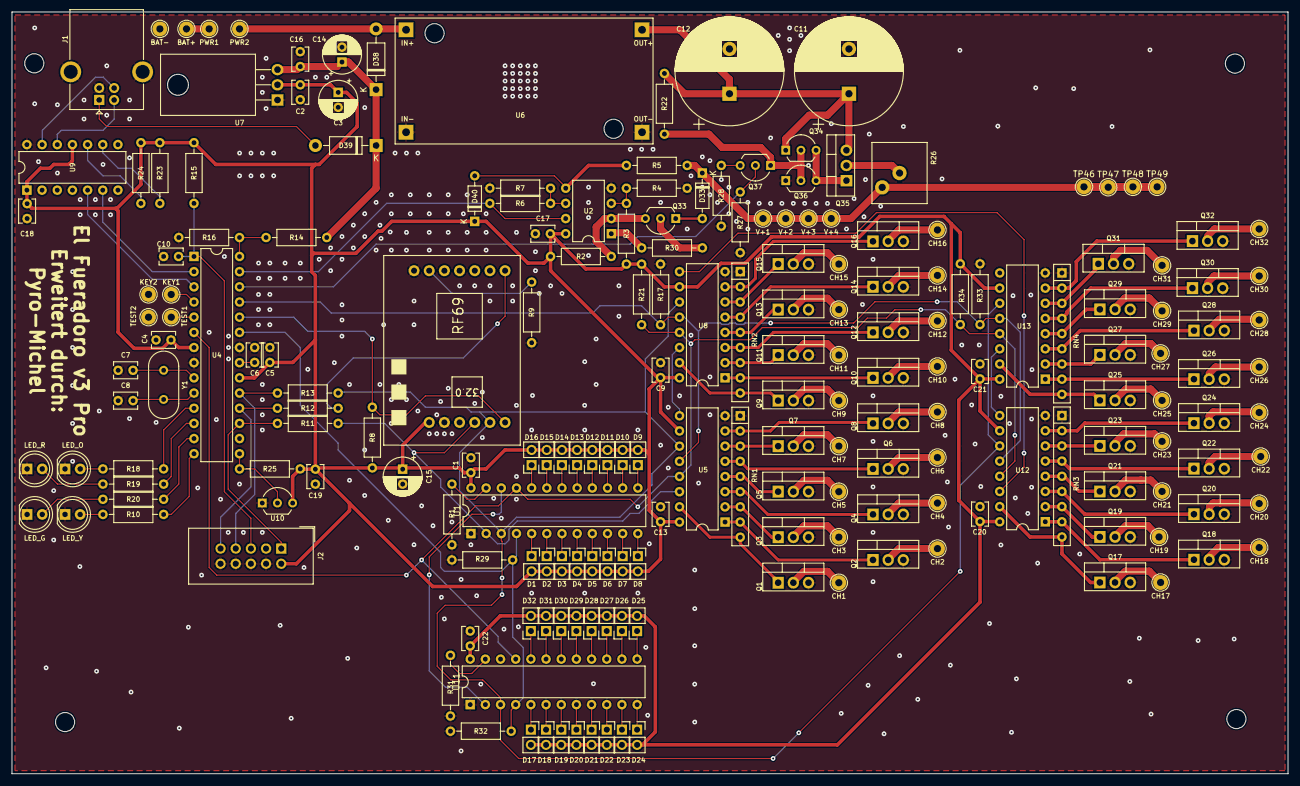
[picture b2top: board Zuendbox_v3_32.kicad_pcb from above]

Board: 2 copper layers, 213.6 x 127.5 mm, 201 parts (0 on the bottom side), 156 nets.

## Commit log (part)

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2014-12-29 Fixed Hardware-SPI-problem which was due to double usage of identical variables for RFM12 and RFM69.
2014-12-31 Recommit after bad changes (Rev. 85)
2014-12-31 Replaced HARDWARE_SPI by HARDWARE_SPI_69 and HARDWARE_SPI_12 respectively during initialization. Reduced SPI-frequency.
2015-01-01 Only allowing remote reconfiguration of device numbers when device is not armed
2015-01-01 Corrected wrong ID-order and unified ID-order in other cases to unique before slave
2015-01-01 LCD lines are now written completely, no leftovers from former commands
2015-01-02 Bugfixes and manual update
2015-01-03 Error correction
2015-01-06 Omitting AFC Fixing issue of slow restart when not connected to terminal program Setting uart-timeout to realistic value Added confirmation-dialogue to remote ID-update Further bugfixes and cosmetic 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
2015-01-07 Rx-Tweak for RFM69 to avoid deadlocks
2015-01-08 Found and implemented a way to find out if connected device is a transmitter or a ignition box. Now it should be impossible to configure a ignition box as transmitter.
2015-01-09 Added security features and device-type-display in configuration routine.
2015-01-09 Further updates and cleanups
2015-01-09 AFC back in charge
2015-01-10 Added repeats to every transmission, not only ignition orders
2015-01-11 Buxfixes on multiple transmitting.
2015-01-12 V 111
2015-01-13 RFM can now be read out via UART (especially interesting for RFM69)
2015-01-15 Big manual update! Some adjustments in update-software to avoid crashes. Reducing of screen-output messages to save memory.
2015-01-16 Code documentation should now be completely in English. Moved address-save-function to other module.
2015-01-16 New repository structure
2015-01-16 Added EAGLE files!
2015-01-18 Added bill of materials
2015-01-20 Added size-information-output for Hexfiles/build_hexfiles.bat Extended manual and added BOMs BOM-Update (final one, hopefully!)
2015-01-20 The manual is still growing
2015-01-21 Layout fixes Additions to manual once again
2015-01-22 Manual update
2015-01-28 Some GUI-preperations!
2015-01-29 Code size optimization Initial blinking now shows slave-id
2015-01-29 Ladies and Gentlemen, we have a GUI! To check it out, the newest firmware has to be flashed on every device first!
2015-01-30 Strict transmitter-ignition device separation
2015-01-31 Secure start-up-sequence Better GUI Removed useless empty line on config
2015-02-01 Removed redundant code
2015-02-08 RFM-access added to GUI
2015-02-21 Drill distance adjusted, layouts up to date
2015-03-10 Only some additional whitespaces
2015-03-13 Formatting...
2015-03-16 Manual-sources added
2015-03-22 Manual...
2015-03-25 Manual formatting
2015-03-30 RFM69-tests
2015-03-31 Updated Manual Still trying to get better config for RFM69
2015-03-31 Updated repository-URL in manual
2015-04-06 Some more pictures in the manual + additional information New RSSI-timeout-interval for RFM69 Terminal display improvement
2015-04-07 Removed unnecessary on-off-commands Rx-Restart on timeouts now part of function rfm_receiving() Rx-Restart on timeouts removed from pyro.c
2015-04-08 Added missing chip-selection Improved bandwidth-related settings
2015-04-08 Updated hexfiles
2015-04-09 Shrink repository
2015-04-12 Deleted files not necessary for compilation of the manual
2015-04-12 Optimized RSSI-threshold for RFM69 Corrected cable lengths in the manual
2015-05-02 New added GUI-content to manual
2015-05-05 RSSI-value added to LCD
2015-05-07 Manual corrections and improvements
2015-05-10 Manual improvements
2015-05-13 Manual
2015-05-20 Took care of unused pin
2015-05-21 Manual improved, clarified ISP connection
2015-06-09 Added compatibility comment to rfm69.c Manual updated and a bit more error corrected
2015-07-03 Manual modifications
2015-07-11 Some improvements in the manual
2015-07-18 Updated the manual once again
2015-07-24 Manual update (RFM-access)
2015-07-26 Added link to firework
2015-08-13 New Eclipse-Version (Mars)
2015-08-13 Added function descriptions to 1wire-lib
2015-08-14 New pictures to show PyroIgnitionControl-configuration
2015-08-14 Funny test
2015-08-15 Case-modding-section extended
2015-08-16 Incorporating recent changes
2015-08-18 Manual size shrunk, pictures resized/resampled
2015-08-25 New GCC-compiler version
2015-09-06 Optical improvement on manual transmission
2015-09-20 Some debugging in the manual
2015-11-09 1-wire-timing corrected
2015-11-11 Better temperature calculation routine
2015-11-13 Unitary source-code formatting No functional changes
2015-11-16 Formatted source code Manual update (Credits)
2015-11-18 Sourcecode beautification Added disabling of shift-registers before reset Manual updated Updated hexfiles
2015-11-22 1-wire-fix in unused function, not really relevant for system Code-translation and beautification
2015-12-01 Option to use hardware-spi with shift register added
2015-12-01 Added missing newline in manual sending routine
2015-12-01 Higher output power for RFM59
2015-12-02 Reset transmission power to 8 dBm Hexfiles updated Manual layout improved
2015-12-02 Code formatting
2015-12-03 Created a high-power-version of the Atmega328p-RFM69-firmware, where 13 dBm is the standard output power of the radio module.
    Manual updated and reformatted
2015-12-04 Extended info on RSSI
2015-12-13 Added datasheet-links to manual Table-unification
2015-12-14 Linebreaks and thesaurus
2015-12-21 Removed the "channel already fired?"-checks
2015-12-21 Manual changes
2015-12-27 Changed Slave-ID-blinking from green/orange to yellow/orange
2015-12-29 Update pyro.c
    Wrong blinking sequence fixed
2015-12-29 Hexfiles updated
2016-02-24 Corrected spelling error
2016-03-06 Added windows-GUI-update tool
2016-03-17 Changed while-condition order to guarantee for proper timeouts (C shortcut-evaluation)
2016-03-17 Added windows-update-gui to manual Some more "shortcut evaluation"-driven changes
2016-03-21 More sophisticated method of calculating Tx-Timeout
2016-03-21 New tool for controlling ignition schemes (no manual update yet)
2016-04-23 Added Gerber Files
2016-04-26 Added hints for double ignition
2016-05-03 GCC version now displaying before build Built hexfiles with GCC 6.1
2016-05-04 Improved build_hexfiles.bat
2016-05-04 Improved build-switches, smaller hexfiles!
2016-05-06 No substantial change, just --relax to -mrelax
2016-05-06 Compiler options changed for Eclipse-project
2016-05-10 Initial transmitter sequence now compliant with loopcount mechanism
2016-05-29 Added LCD-timeout
2016-08-20 Type errors
2016-09-07 New styling for the manual
2016-09-07 Small bugfixing from last update
2016-09-08 Valid eBay-links
2016-09-14 Manual updated
2016-09-16 Unit spacing and footnotes with updated PDF
2016-09-30 Optimized timeout in RFM69 Manual update on radio-range
2016-11-24 Correct transmission of transmitter's armed-status
2016-12-01 Handling of pin in case of missing temperature sensor
2016-12-10 Preparations for next generation, old boxes will still be fully supported
2016-12-18 Transmitter-arming implemented in GUI
2017-05-25 Larger update: Frequency deviation adaption Bills of Material No more RFM12-support
2017-05-28 Implemented AES-encryption
2017-07-13 Hexfiles compiled with new AVR-GCC 7.1 Manual corrections
2017-07-14 Only newest manual version available
2017-07-14 One more try
2017-07-22 Bugfix in Zündbox_v2-Gerber-Files Kompiliert mit AVR-GCC 8
2017-08-05 Manual update Display of internal AES-Key for comparison
2017-10-01 BOM correction
2017-10-25 BOM fixes
2017-12-15 Korrektur sprachlicher Fehler im Handbuch
2018-01-05 Angleichung von Handbuch und Layouts
2018-01-22 Dynamisierter Rx-Timeout
2018-05-14 Workaround for string comparison
2018-08-04 Cumulative update of some changes
2018-08-15 Changes in v3-firmware
2018-08-15 Impedance listing
2018-08-20 v3-bugfix for impedance calculator
2018-08-21 Project settings for v3
2018-08-22 Automatic dummy conversion for every ADC-measurement
2018-09-08 Working and tested v3 with channel LEDs and impedance measurement
2018-09-08 Added some v3-documentation
2018-09-20 Implemented impedance re-reading upon disarming
2018-10-15 v3 impedance update now triggerable by turning key switch
2018-11-03 Consistency
2019-01-11 Setting v3 as standard for flash
2019-01-24 RFM-Adapter-Gerber Files
2019-01-26 Finally added some raspEasyFire-stuff to the manual
2019-01-27 Additional subsection
2019-03-16 AVRDUDE update
2019-03-16 Intelligent Bootloader-Flasher avoiding verification error for EFUSE
2019-05-21 Time triggered channel measurements
2019-05-25 Reorganized ignitions and interrupts
2019-05-30 Impedance read condition refined
2019-05-31 Minor fixes on transmission delays
2019-06-10 Added datecode and timecode to firmware files for easier version recognition
2019-06-29 Timestamps and manual
2019-09-16 New compiler for hexfiles Some additions to the manual
2019-09-17 Some more information on bootloader-flashing in the manual
2019-09-25 Preparations for easier future expandability to more than 30 boxes
2019-09-29 Timestring-Fix and LED signaling bugfix
2019-09-29 Timestamp fix and LED fix for v3
2019-10-04 Found final startup LED solution
2019-10-04 Flexible ID limit, can be provisioned at compiletime
2019-10-06 New buildscript taking MAX_ID as parameter and checking for plausibility
2019-10-11 Fixed another MAX_ID/MAX_COM_ARRAYSIZE confusion Hexfiles compiled with MAX_ID=50
2019-10-22 Extendability improvements
2019-11-24 Update README because of RawGit shutdown
    RawGit will be shut down in the near future (we are already past its "served at least until" time), so a change to the jsDelivr service is a good idea).
2019-11-27 Impedance transmission ready for 32 channels
2019-12-08 Replaced hardcoded channel maximum number with define
2019-12-10 Encorporated some cppcheck hints
2019-12-15 Spaces
2019-12-16 Make the channel number a part of the box parameters
2019-12-26 Adjustable ignition time
2020-01-02 Gerber
2020-03-16 Disable v3 channel LEDs when arming slave
2020-03-16 Bugfix concerning impedance measurement on armed slaves
2020-03-28 KiCad schematic files for Raspberry Pi pcb
2020-03-30 Extended duration of channel LED test phase
2020-03-31 Typo
2020-05-12 Changed RF parameters (smaller deviation, smaller rx bandwidth)
2020-05-18 New image naming scheme, omitting 8 dBm versions
2020-05-30 Gerber files for RFM69HCW adapter
2020-05-30 Bugfix and code cleanup for proper function of RFM69HCW
2020-06-08 Corrected wrong GPIO for RFM-CS in v1/v2
2020-06-09 Added RFM init fail indicator (orange and green LED permanently on)
2020-06-15 User manual
2020-11-22 RSSI-Threshold remotely programmable
2020-11-23 Delivering RSSI value as part of parameter protocol Fixed typo in manual
2021-01-17 Timeout adjustment
2021-01-17 Packet delay config
2021-01-19 Check for incoming packets during impedance measurement and stop measuring if required
2021-02-06 Debouncing and Minimodul-Firmware
2021-03-28 Eclipse update
2021-04-02 Multicue capabilities
2021-04-30 Mini module operating frequency, new bootloader and test routine
2021-05-02 Battery voltage calculation for Mini module
2021-07-30 MiniModul-Bugfix: Channel LEDs now turning off after being triggered remotely
2021-08-01 New El Fueradoro Logo
2021-08-18 Igniter choice bugfix
2021-08-21 Reset channel timeout counter every time a channel is triggered - making retriggering possible while channel already active
2021-09-06 Implementation of squelch value auto-adjustment
2021-09-07 Amendments for Minimodul
2021-09-07 Hexfile update
2021-09-08 Control loop smoothing
2021-09-14 Changed output for terminal command hw to enable device identification (number of channels and RFM type)
2022-01-12 Optimized wait time after packet reception
2022-02-24 Add some to ignition time window
2022-03-10 Introducing delay between repetitions to give Rx a better chance to sync
2022-03-27 Frequency change possibility
2022-03-29 Frequency setting option
2022-03-31 Fixed inconsistent init of RFM register
2022-04-01 Avoid timeout if other boxes send impedance lists
2022-04-01 Handling timeout case for impedance measurement setting
2022-05-22 Auto squelch finetune: don't open up more in armed state if certain level is already reached
2022-06-29 Force number of DM13A channels to a multiple of 16
